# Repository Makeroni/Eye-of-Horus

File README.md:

# Eye-of-Horus

Eye of Horus is an open source platform to control any device just looking at them. The project (hardware & software) was built from scratch during the Space Apps Zaragoza to solve the Space Wearables challenge. This device could help engineers from NASA and astronauts on their tasks. The system combines eye tracking with a frontal camera to know where you are looking. The target devices are identified using light beacons (similar to LiFi technology) and controlled with wireless protocols.

![Logo][logo] Interacting with objects just looking at them has always been a dream for humans.

NASA engineers doing lab and field work often need to operate with computers and other tools but in some situations this interaction is not easy and may cause them to interrupt their activities. The absence of gravity hinders the mobility of the astronauts inside the station and may affect their work and safety. We accepted the Space Apps challenge for creating a wearable accessory that could help people interacting with computers, electronic devices and also everyday things just looking at them.

1. **Challenge:** The challenge is to design and build a wearable accessory that could be useful for the NASA ground engineers and also astronauts in their lab or field activities. The device would facilitate their work through a natural interface so they can do different things without using their hands. Thanks to it, they will be able, for instance, to interact with a distant control panel just looking at it.

2. **Wearables:** Wearable refers to the set of electronic devices which are incorporated in any part of our body that continuously interact with the user and other devices in order to perform a specific function. Smart watches, sports shoes built-in with GPS and bracelets that monitor our health are examples of this technology which is increasingly present in our lives. One of the best known wearables is Google Glass. Our device could be designed as an accessory to use with Google Glass to simplify the hardware and reduce its costs.

3. **3D printing:** The device must be durable and made from a non-brittle material. Due to this, we have decided to make it using 3D printers. This technology is cheap and easy to build so the device could be replicated worldwide or even in the space. NASA engineers could improve the device in their labs in a minute and astronauts could produce or fix it using the 3D printers at the station.

4. **Open Source:** We believe open knowledge is contributing to a better world and Eye of Horus is designed as an open source platform, both hardware and software.
The schematics and the implemented software can be found in the project Github repository, allowing people to modify, improve and redistribute their contributions.

5. **Internet of Things:** The Internet of Things (IoT) is a growing trend that extends internet connectivity beyond traditional devices like computers, smartphones and tablets to a diverse range of devices and everyday objects. This revolution increases the possibilities of the Eye of Horus allowing you to control the light level of your kitchen or turning on the coffee machine just using your vision. Therefore, the device must have built-in wireless capabilities, which is the base of IoT.

6. **Low Cost Solution:** We have developed a simple and low cost solution to detect and identify the objects in our surrounding. Infrared leds are used as light beacons (similar to LiFi technology) emitting different frequency pulses for each device (PC, camera, TV, microwave...). The frontal camera of our dispositive detects this light, differentiating and communicating the objects when you look at them.

# APPLICATIONS

Eye of Horus lets you interact with devices and objects just looking at them. The main application in the current challenge is to improve the work and safety of the NASA ground engineers and astronauts but this device could also make common people's lives easier:

- -Disability. People with functional diversity or who is hospitalized could use it to perform tasks which would be impossible due to their reduced mobility.

- -Driving safety and control. Thanks to our device, drivers could interact with the radio or car phone with both hands on the wheel. Their eyes could be also monitored to detect drowsiness or lack of attention on the road and prevent a potential accident.

- -Entertainment. It could be used as an eye-controlled mouse to play video games and position the targets just looking at them.

# HARDWARE

The hardware development efforts were split in two different branches:

- 1) Design and fabrication of the 3D printed case and frame.

- 2) Design and assembly of the required electronic components.

### Rubén Martín, member of Eye of Horus:

> The hardware is HARD!

 **3D Printing** 

The casing was designed to integrate the electronic components of the system. It consists of several 3D printed pieces to hold and position the camera, the infrared lights and allocate the electronics and batteries.  The complete 3D model can be viewed online in the following [link](http://p3d.in/e/JN2Oy+load).

We started with a simple design that has been improved to the current version:

- *Version 1*: The first goal was to design and fabricate a case which could be fitted as an accessory of the Google Glass. A replica was 3D printed as we did not have an actual product. The casing consists of a small box containing the battery and the processor connected through an USB wire to the camera. An articulated tube which ends in the camera holder and the infrared lights allows the system to be mobile and frame the eye pupil.

- *Version 2*: In the second version, which is the end of this prototype, the molding of the glasses is independent and functional without the need of the Google Glass. The look and the fastening system of the electronic components have been improved in this second version.

![Designed frame and casing][3d]

 **Electronic design** 

- **Eye Tracking device**

This part corresponds to the wireless system that captures and analyzes the eye pupil images under infrared illumination.

During the development process, several iterations have been made improving the prototype features and finally designing a printed circuit board (PCB) that could be manufactured with a low cost.

***Prototype 1***: A first prototype was built over the table with no case to test hardware and software.

![Prototype image][proto1]

The parts used in the different prototypes are common:

-  [VoCore v1.0](http://vocore.io/):  VoCore is a coin-sized Linux computer with wireless capabilities. It is also able to work as a fully functional router. It runs OpenWrt on top of Linux and contains 32MB SDRAM, 8MB SPI Flash and using 360MHz MIPS processor.

- Power circuit: It includes a system DC/DC which supply 5V to the circuit thanks to a lithium battery

- [Camera](http://www.alibaba.com/product-detail/7-1mm-mini-video-endoscope-camera_515483490.html): an small size USB endoscope camera was disassembled to remove the infrared blocking filter and replace it with a band pass filter with the oposite effect. This task was complicated due to the small size of the optical elements.

![Removing camera filter][camera]

- IR leds: infrared leds are responsible to illuminate the eye. The pupil is an aqueous medium that absorbs this light and results in a dark spot clearly visible in the images.

- Bandpass filter: a lens that filters the non-infrared frequencies of light emphasize the monochrome effect and prevents ambient light from affecting the system.

***Prototype 2***: Once the basic software and hardware was validated, a second version was developed to complete and integrate the system using the 3D printing models of the first version of the casing.

![Prototype image][proto2]

The system was modified to overcome the following hardware problems:

- Remove the electronic noise emitted by WiFi shield that affects data transmission in the camera wire.

- Correct the placement, orientation and intensity of the infrared LEDs for a correct eye pupil illumination.

All electronics components of the prototype were replicated in the second version to get a better finish of the product.

![Prototype image][proto3]

![Prototype image][proto4]

The assembly is the result of the first model of the product. It could be an addition to Google Glass using its front camera like a data gathering system of the physical world.

***Prototype 3***: On this part, a printed circuit board was designed based on the information obtained from the previous prototypes. It would allows a low cost and replicable electronic device. 

![Designed printed circuit boards][schematics]

This is a open source project, so all schematics are available. Anyone can download, edit and manufacture the device.

- **Light beacon device**

A prototype was designed using infrared flashlight pulses with adjustable frequency. This light, only visible in the front camera thanks to a band-pass filter, allow to differentiate the targeted devices.

![Light beacon device][beacon]

The system also integrates a bluetooth low energy (BLE) module which can receive requests from other devices. In our case, a computer linked with other BLE module is in charge of sending the turn on/off request when the main device indicates that the user is in front of the object and the eye tracking reveals that is looking at the beacon (in the example it would be a light lamp).

![Infrared images][ir]

The integrated components in this prototypes are:

- [Serial Bluetooth 4.0 BLE Module](http://www.tinyosshop.com/index.php?route=product/product&product_id=705): responsible for the communication of BLE with PC.

- [Relay control module](https://www.sparkfun.com/products/11042): to control a device connected to the network

- [Arduino Pro mini](http://www.arduino.cc/en/pmwiki.php?n=Guide/ArduinoProMini): the main microcontroller in charge of communicating with other modules and components.

- Infrared LED: responsible for carrying out the lighting flash.

# SOFTWARE

Our final goal is to obtain an autonomous device but during the weekend the software development was divided in two blocks: server and client. Server software is running inside the Eye of Horus while the client is running on a laptop computer.

**Server**

![Testing OpenWrt in the Vocore][openwrt]

This part of the software is executed in the VoCore module, a coin sized linux computer suitable for many  applications. This module acts as a server running OpenWrt, a Linux distribution for embedded devices.

The server software is in charge of:

- Capturing the video captured by the camera

- Streaming the data over WiFi using a lightweight webserver

**Client** 

![HTML5 eye interface][eyeint]

This part is in charge of:

- Receiving the video stream

- Processing the images of the eye in order to detect the center of the pupil

- Provide a user interface to calibrate the system

- Control the mouse in the laptop computer according to the coordinates dictated by the eye

The video stream in the client was processed in real time using HTML5. A segmentation library was developed from scratch to threshold the images and analyze its morphology to detect the pupil and compute its center of mass.

![Developed real time image segmentation library][code]

At this point, the user has a mouse controlled by his eye and can interact with any 3rd party software installed in the computer.

A demo of the client sofware recognizing the center of the pupil can be seen in our [website](http://makeronilabs.com/sites/nasa/eye_of_horus_interface/). You can play with the range selectors in order to see how it affects the recognition and reach optimal calibration when only the pupil is highlighted. The system will consider the center of gravity of the highlighted area as the coordinates where the eye is pointing. Calibration is very important and it may depend of the illumination. Thats the reason why the Eye of Horus has 4 leds illuminating the area of the eye. The pupil detection system has proven to be quite robust with the illumination provided by the device.

# DEMOS

Here you can find some examples of use:

 [Eye of Horus - Open Source Eye Assistance](https://vimeo.com/125373219) 

 [Eye of Horus Demo 1](https://vimeo.com/125396508) 

 [Eye of Horus Demo 2](https://vimeo.com/125396713) 

 [Eye of Horus Demo 3](https://vimeo.com/125396803) 

 [Eye of Horus Demo 4](https://vimeo.com/125396891) 

# FUTURE

The most important part of this project is the viability and profitability. We believe this project is highly sustainable. We can create a crowdfunding campaign using all the documentation.

### Borja Latorre, member of Eye of Horus:

>Never think about the future because it comes soon.

![The future][future]

We have the support of the City of Zaragoza and other incubators project to move forward. We also collaborate with numerous technological associations in our city. We have succeeded in 48 hours a functional prototype to show our system. It is easy to build, cheap and technological.

### Jose Luis Berrocal, member of Eye of Horus

> People say that space is unlimited. We also believe that our project has no limits. 

# OUR SPACE APPS WEEKEND:

During this amazing weekend we met very nice people, participated in one of the most important experiences of our lives, learning at every moment and developing after 48 hours of hard work a final product. 

![Our space apps weekend][weekend]

### Luis Martín, member of Eye of Horus

> A unique experience, an amazing team and an impressive project. 

Here you can see our weekend and several milestones that have marked the achievement of the project:

- **SATURDAY**: 

- **9:00**: Space Apps Zaragoza START.

- **10:00**: Make your team, present your idea: We want to participate in the Wearables Challenge developing a real product involving hardware and software.

- **10:30**: Brainstorming: We have a 3D printer, some microcontrollers, electronics components, a solder... what can we do?.

- **11:00**: State of the art: We decide to create a device to eye tracking monitoring capable to control any electrical device mixing the tracking of the eye and a frontal camera that analyze the real world. We start searching some information about actual application of this technology and other similar projects.

- **11:30**: Meeting: We show the information collected to the team.

- **11:45**: Hardware: We design a first assemble (VOCORE board, DCDC board, battery and camera) to bring to the software developers a prototype to work with it.

- **12:00**: Software: We start to program the main code. This HTML code control and track the eye movements.

- **12:00**: Hardware: We create a 3D design of the first prototype. We develop the electronic case and the structure for placing the camera system on the head of a person.

- **12:45**: 3D printing: Our 3D printer (TAZ4 Lulzbot) start to print the first samples of the case. We rebuild the designs in other to improve our models.

- **13:45**: Software: We finish the basic code in HTML5 to track the eye movement.

- **14:00**: It is time to eat….PIZZA!! and talk with other team about their projects. Co-working 100% Thanks to the Space Apps Zgz organization.

- **14:30**: Meeting: We define the next millestones of the project. We decide to create a web interface to calibrate the device.
- **15:00**: 3D printing: We improve our designs in order to build the first version of the case. We print it!

- **15:30**: Software: We want to control the mouse of the computer with our eye as a example of application. We design a web interface to test and calibrate the device. 

- **17:00**: Hardware: We finish the power circuit assembly for the first prototype.

- **18:00**:  Software: We develop the web interface and the PHP code. This code is used to control the PC mouse using our eye track.

- **19:00**:  Documentation: We start to documentate all the software.

- **20:00**: It is time to eat….PIZZA AGAIN!! Night is coming in Zaragoza.

- **22:00**:  Night meeting: We talked about what happened during the day.

- **00:00**: We go to Makeroni space (a local technological association) to finish the first hardware prototype in the night.

- **SUNDAY**: 

- **4:00**: It is time to sleep

- **9:00**: Begins the second and final day. A cup of coffee and the batteries recharged.

- **10:30**: Meeting: We start the day with a real prototype and the basic software. This day we want to control a light, our computer and the TV with the eye like an example of use to use it for the presentation.

- **11:00**: Hardware: We have a lot of noise in the camera signal in the prototype. We can not continue working. We start to investigate where is the problem.

- **11:30**: Software: We use Processing IDE to create some examples of applications. 

- **11:45**: Hardware: The device still fails. We dismount the system piece by piece to find the error.

- **12:00**: Presentation: The presentation is a very important point in this event. We start before lunch.

- **12:00**: Software: We want to show our eye in the presentation and control it with our eye. So we decide to make the presentation with Reveal JS / HTML.

- **13:45**: Hardware: After several test and changes (battery, microcontroller, dcdc circuit) we find the problem. The wifi in our device makes a loud noise and the cable used was not shielded.

- **14:00**: The last meal before the presentations .... it could not be any other thing than PIZZA!!

- **14:30**: Presentation: We still working in a "amazing" presentation with slide eye control but we need a functional prototype.

- **15:00**: Software: We modify Reveal JS presentation to add the eye tracking function.

- **15:30**: Software: We want to control the mouse of the computer with our eye as a example of application. We design a web interface to test and calibrate the device. 

- **17:00**: General: We prepare hardware and software for the final part of the event.

- **18:00**:  PRESENTATION TIME: It's time to present our project to all attendees and prove that Eye of Horus is the best.

- **20:00**: Finish one of the best experiences of our lives.

# ABOUT US

The four members of the team have different technological backgrounds as electronic engineering, physics and computer science but we all share passion for making all kind of inventions mixing any available technology.

We are all members of [MAKERONI LABS](http://makeronilabs.com), a non profit that was born in Zaragoza in 2012 following the MAKER movement that is currently shaking the world.

Its main purposes are:

- Promote a collaborative workspace for the development of new technologies.

- Promote the dissemination of new technologies; both projects developed by members of the association, as other people. 

To fulfill these purposes are working on:

- Create and maintain a physical or virtual, collaborative work space.

- Promote and coordinate the development of technological projects for companies and individuals, by members of the association.

- Promote the capacities of members of the association in competitions, talks and exhibitions.

- Conduct outreach to the diffusion of new technologies activities.

### Makeroni Team

> We did this Open Source project for the Space Apps Challenge 2015. 
> We hope you will like it, use it for your inventions and in any way contribute to the project!

# MORE INFO

The Eye Of Horus project in our site: [Eye of Horus Project](http://makeronilabs.com/proyectos/37-eye-of-horus-open-source-eye-assistance) 

[logo]: http://makeroni.github.io/Eye-of-Horus/img/logo.png
[3d-model]: http://makeroni.github.io/Eye-of-Horus/img/3d-model.gif
[proto1]: http://siminelaki.org/noname/nasa/photos/prototype-0.png
[proto2]: http://siminelaki.org/noname/nasa/photos/prototype-1.png
[proto3]: http://siminelaki.org/noname/nasa/photos/prototype-2.png
[proto4]: http://siminelaki.org/noname/nasa/photos/prototype-3.png
[beacon]: http://siminelaki.org/noname/nasa/photos/prototype-4.png
[eyeint]: http://siminelaki.org/noname/nasa/photos/prototype-5.png
[future]: http://siminelaki.org/noname/nasa/photos/future.png
[weekend]: http://siminelaki.org/noname/nasa/photos/weekend.png
[schematics]: http://siminelaki.org/noname/nasa/photos/schematics.png
[3d]: http://siminelaki.org/noname/nasa/photos/3d-model.png
[openwrt]: http://siminelaki.org/noname/nasa/photos/openwrt.png
[ir]: http://siminelaki.org/noname/nasa/photos/ir.png
[camera]: http://siminelaki.org/noname/nasa/photos/camera.png
[code]: http://siminelaki.org/noname/nasa/photos/code.png

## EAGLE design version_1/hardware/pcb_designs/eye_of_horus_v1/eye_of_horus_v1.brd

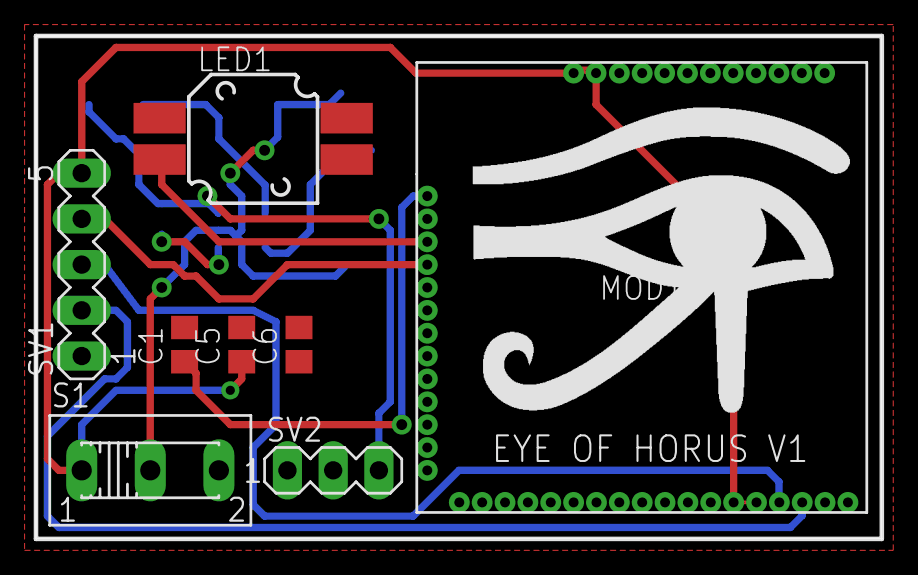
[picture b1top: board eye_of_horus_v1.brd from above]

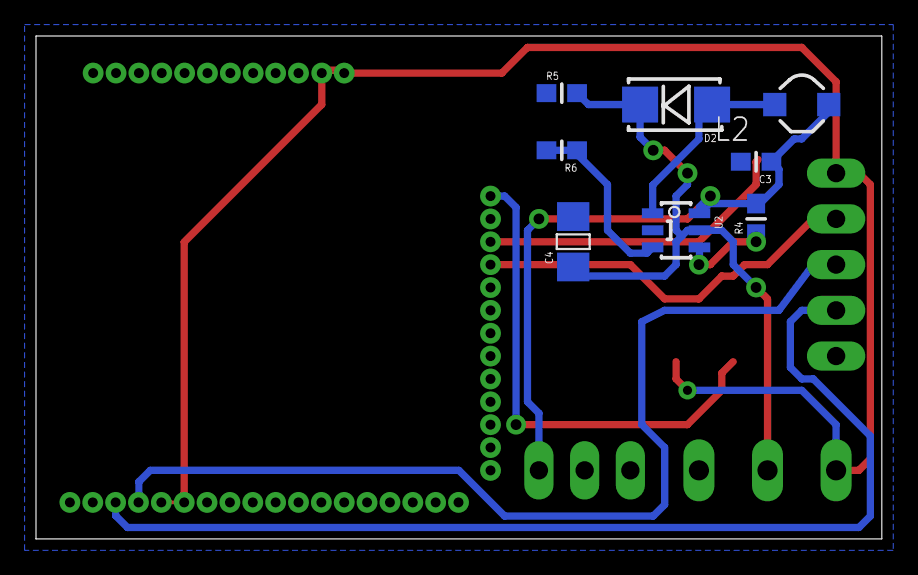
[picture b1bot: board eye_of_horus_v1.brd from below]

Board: 2 copper layers, 47.0 x 27.9 mm, 16 parts (8 on the bottom side), 12 nets.

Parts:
C1, C5, C6: C0805
C3: 10uF; 0603
C4: 22uF; 1206
D2: MBRA210LT3G; SMA-DIODE
L2: 2.2uH; 1_3X1_3
LED1: LEDLUMILED; LUMILED
MOD1: VOCORE_V10A
R4: 1M; 0603
R5: 95.3K; 0603
R6: 30.9K; 0603
S1: 255SB
SV1: MA05-1
SV2: MA03-1
U2: LTC3426; SOT23-6

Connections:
1V8: C1.1, MOD1.W1
5V: C5.1, MOD1.N1, MOD1.N2, MOD1.S13, MOD1.S14, S1.1, SV1.5
GND: C1.2, C3.2, C4.2, C5.2, C6.2, LED1.4-, MOD1.N3, MOD1.N4, MOD1.S17, MOD1.S18, R6.1, SV1.1, SV2.2, U2.2
GP09: LED1.2+, MOD1.W3
GP22: MOD1.W4, SV1.4
unnamed: D2.A, L2.P$2, U2.1
unnamed: R4.1, U2.4
unnamed: C4.1, D2.C, R5.2, S1.2, U2.5
unnamed: R5.1, R6.2, U2.3
USB_N: MOD1.S15, SV1.3
USB_P: MOD1.S16, SV1.2
VBAT: C3.1, L2.P$1, R4.2, SV2.3, U2.6

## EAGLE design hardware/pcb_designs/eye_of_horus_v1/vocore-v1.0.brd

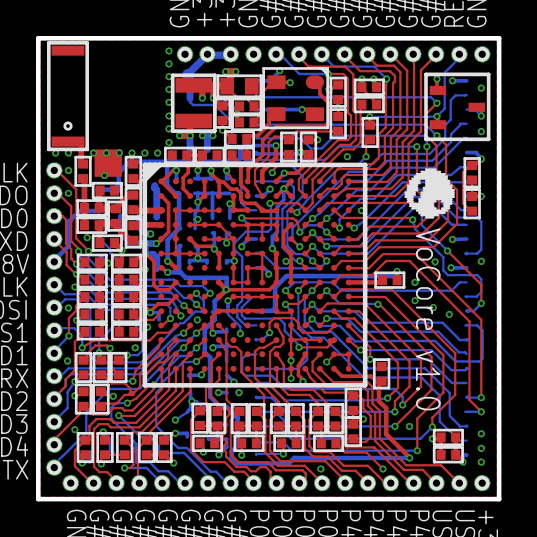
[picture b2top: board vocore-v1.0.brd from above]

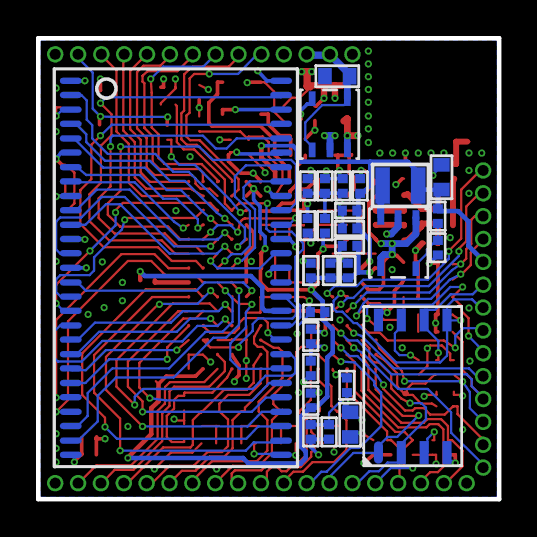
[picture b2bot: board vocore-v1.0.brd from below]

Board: 4 copper layers, 25.6 x 25.6 mm, 146 parts (29 on the bottom side), 113 nets.

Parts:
C2, C4, C6, C7, C8, C9, C10, C14, C15, C16, C17, C18, C35, C36, C37, C38, C40, C42, C43, C48, C50, C77, C79, C84, C92, C93, C98, C104, C108, C109, C110, C111, C112, C113, C114, C161, C251, C279, C387, C388, C389, C390, C391, C414, C422, C443: 0402; 0402_1PRIMARY
C103, C105, C106, C107: 0603; 0603_1PRIMARY
CON2: 5020; 5020_1PRIMARY
D1: 0402; 0402_1PRIMARY
L11, L12: 0402; 0402_1PRIMARY
L14, L15: 0806; 0806_1PRIMARY
PB00, PB01, PB02, PB03, PB04, PB05, PB06, PB07, PB08, PB09, PB10, PB11, PB12, PB13, PB14, PB15, PB16, PB17, PB18: PORT_1PIN_DECAL; PORT_1PIN_DECAL_1PRIMARY
PL01, PL02, PL03, PL04, PL05, PL06, PL07, PL08, PL09, PL10, PL11, PL12, PL13, PL14: PORT_1PIN_DECAL; PORT_1PIN_DECAL_1PRIMARY
PT01, PT02, PT03, PT04, PT05, PT06, PT07, PT08, PT09, PT10, PT11, PT12, PT13, PT14: PORT_1PIN_DECAL; PORT_1PIN_DECAL_1PRIMARY
R1, R8, R26, R27, R28, R29, R50, R55, R56, R57, R58, R67, R68, R69, R70, R71, R94, R95, R107, R118, R119, R142, R144, R150, R154, R189, R192, R193, R212, R293, R300, R308, R318: 0402; 0402_1PRIMARY
SR1, SR2: 0402; 0402_1PRIMARY
TEST1: TEST_POINT_GND; TEST_POINT_GND_1PRIMARY
U1: TFBGA196; TFBGA196_1PRIMARY
U3: SO8; SO8_1PRIMARY
U8, U9: LDO1; LDO1_1PRIMARY
U25: U4; U4_1PRIMARY
U33: Y1; Y1_1PRIMARY
U35: TSOP2-54P-400MIL; TSOP2-54P-400MIL_1PRIMARY

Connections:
1V8_FB: R67.1, R68.2, U8.5
1V8_SW: L14.1, U8.3
3V3_FB: R69.2, R70.1, U9.5
3V3_SW: L15.1, U9.3
$$$22498: U1.7, U33.1
$$$22629: C15.2, R212.1, U33.3
+1.2V: C16.1, C93.1, C98.1, C104.1, C109.1, C110.1, C111.1, U1.10, U1.23, U1.24, U1.79, U1.85, U1.93, U1.103, U1.107, U1.117, U1.195
+1.8V: C2.1, C106.1, C108.1, C161.1, L14.2, PL05.1, R68.1, U1.8, U1.86
+3.3V: C9.1, C17.1, C42.1, C84.1, C92.1, C105.2, C107.1, C112.1, C113.1, C114.1, C251.2, C387.1, C388.1, C389.1, C390.1, C391.1, C414.1, C422.1, C443.2, L15.2, PB18.1, R69.1, R71.1, R144.1, R192.2, R293.1, SR2.1, U1.9, U1.15, U1.52, U1.57, U1.59, U1.75, U1.80, U1.89, U1.94, U1.100, U1.108, U1.114, U1.131, U1.132, U1.133, U1.134, U1.179, U3.8, U8.1, U8.4, U25.3, U35.1, U35.3, U35.9, U35.14, U35.27, U35.43, U35.49
+5V: C103.1, PT02.1, PT03.1, U9.1, U9.4
EPHY0R_RC: C48.1, R26.2, R28.2
EPHY0T_RC: C50.1, R27.2, R29.2
EPHY4R_RC: C79.1, R56.2, R58.2
EPHY4T_RC: C77.1, R55.2, R57.2
EPHY_RES: R50.2, U1.186
GND: C2.2, C4.2, C6.2, C7.2, C8.2, C9.2, C10.1, C14.1, C15.1, C16.2, C17.2, C18.1, C40.2, C42.2, C43.2, C48.2, C50.2, C77.2, C79.2, C84.2, C92.2, C93.2, C98.2, C103.2, C104.2, C105.1, C106.2, C107.2, C108.2, C109.2, C110.2, C111.2, C112.2, C113.2, C114.2, C161.2, C251.1, C387.2, C388.2, C389.2, C390.2, C391.2, C414.2, C422.2, C443.1, D1.2, L11.2, PB00.1, PT01.1, PT04.1, PT14.1, R1.2, R8.1, R50.1, R67.2, R70.2, R94.2, R95.2, R107.2, R118.1, R119.2, R142.1, R150.1, R154.2, R308.2, R318.2, TEST1.1, U1.1, U1.4, U1.16, U1.18, U1.30, U1.31, U1.32, U1.33, U1.44, U1.45, U1.46, U1.47, U1.48, U1.49, U1.50, U1.51, U1.58, U1.60, U1.61, U1.62, U1.63, U1.64, U1.65, U1.71, U1.72, U1.73, U1.74, U1.76, U1.77, U1.78, U1.90, U1.91, U1.92, U1.104, U1.105, U1.106, U1.118, U1.119, U1.120, U1.121, U1.135, U1.136, U1.150, U1.164, U1.165, U1.166, U1.178, U1.181, U1.182, U1.192, U1.196, U3.4, U8.2, U9.2, U25.2, U33.2, U33.4, U35.6, U35.12, U35.28, U35.41, U35.46, U35.52, U35.54
GPIO0: PT09.1, U1.26
I2C_CLK: PT12.1, U1.28
I2C_SD: PT11.1, U1.27
JTAG_CLK: PT07.1, U1.12
JTAG_RST: PT06.1, U1.11
JTAG_TDI: PT10.1, U1.14
JTAG_TDO: PT05.1, U1.25
JTAG_TMS: PT08.1, U1.13
LED0: PL03.1, R308.1, U1.129
LED1: PL09.1, R154.1, U1.141
LED2: PL11.1, R150.2, U1.144
LED3: PL12.1, R144.2, U1.155
LED4: PL13.1, R118.2, U1.158
LED_WLAN: R142.2, R193.2, U1.127
LED_WLAN+: D1.1, R193.1
P0RN: PB11.1, R26.1, U1.145
P0RP: PB10.1, R28.1, U1.159
P0TN: PB08.1, R27.1, U1.173
P0TP: PB09.1, R29.1, U1.187
P4RN: PB15.1, R56.1, U1.177
P4RP: PB14.1, R58.1, U1.191
P4TN: PB12.1, R55.1, U1.163
P4TP: PB13.1, R57.1, U1.149
RESET: PT13.1, R189.2, U25.1
RESET_PORST: R189.1, U1.38
SDRAM_A0: U1.98, U35.23
SDRAM_A1: U1.111, U35.24
SDRAM_A2: U1.110, U35.25
SDRAM_A3: U1.109, U35.26
SDRAM_A4: U1.126, U35.29
SDRAM_A5: U1.125, U35.30
SDRAM_A6: U1.124, U35.31
SDRAM_A7: U1.140, U35.32
SDRAM_A8: U1.139, U35.33
SDRAM_A9: U1.123, U35.34
SDRAM_A10: U1.154, U35.22
SDRAM_A11: U1.138, U35.35
SDRAM_A12: U1.153, U35.36
SDRAM_BA0: U1.152, U35.20
SDRAM_BA1: U1.168, U35.21
SDRAM_CAS: U1.40, U35.17
SDRAM_CKE: R293.2, U1.39, U35.37
SDRAM_CLK: R300.2, U35.38
SDRAM_CS: U1.137, U35.19
SDRAM_D0: U1.66, U35.2
SDRAM_D1: U1.53, U35.4
SDRAM_D2: U1.54, U35.5
SDRAM_D3: U1.55, U35.7
SDRAM_D4: U1.56, U35.8
SDRAM_D5: U1.67, U35.10
SDRAM_D6: U1.81, U35.11
SDRAM_D7: U1.68, U35.13
SDRAM_D8: U1.82, U35.42
SDRAM_D9: U1.69, U35.44
SDRAM_D10: U1.70, U35.45
SDRAM_D11: U1.95, U35.47
SDRAM_D12: U1.96, U35.48
SDRAM_D13: U1.83, U35.50
SDRAM_D14: U1.97, U35.51
SDRAM_D15: U1.84, U35.53
SDRAM_DQML: U1.122, U35.15
SDRAM_DQMU: U1.167, U35.39
SDRAM_R51: R300.1, U1.112
SDRAM_RAS: U1.151, U35.18
SDRAM_WE: U1.41, U35.16
SPI_CLK: PL06.1, SR1.2, U3.6
SPI_CLK_L: R94.1, SR1.1, U1.169
SPI_CS0: PB06.1, U1.183, U3.1
SPI_CS1: PL08.1, U1.142
SPI_HOLD: R71.2, U3.7
SPI_MISO: PB05.1, U1.156, U3.2
SPI_MOSI: PL07.1, R95.1, U1.115, U3.5
SPI_WE: SR2.2, U3.3
UARTF_CTS: PL02.1, U1.130
UARTF_DCD: PL01.1, U1.116
UARTF_DSR: PL10.1, U1.143
UARTF_DTR: PB07.1, U1.172
UARTF_RIN: PL14.1, U1.157
UARTF_RTS: PB02.1, U1.184
UARTF_RXD: PB03.1, R192.1, U1.171
UARTF_TXD: PL04.1, R119.1, U1.128
UARTL_RXD2: PB04.1, R318.1, U1.185
UARTL_TXD2: PB01.1, R107.1, U1.170
UPHY_RES: C43.1, R8.2, U1.193
USB_M: PB16.1, U1.180
USB_P: PB17.1, U1.194
WL_ANT: C36.2, C279.1, L12.2
WL_ANT_C: C279.2, CON2.2
WL_RF0_OUTL: C35.2, C36.1, C37.1, L11.1
WL_RF0_OUTN: C38.1, U1.43
WL_RF0_OUTP: C35.1, U1.29
WL_RF0_OUTR: C37.2, C38.2, C40.1, L12.1
WL_V12_CAP: C4.1, C6.1, C7.1, C8.1, U1.5, U1.17, U1.19, U1.36, U1.37
WL_V12_PLL: C14.2, U1.20, U1.34, U1.35
WL_V12_RES: C10.2, R1.1, U1.22
WL_V33: C18.2, U1.6
WL_X2: R212.2, U1.21

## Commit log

2015-04-16 Improve the eye interface
2015-04-16 Hardware folder
2015-04-18 Rename 3d model folder
2015-04-18 Create gh-pages branch via GitHub
2015-04-18 Add logo image
2015-04-18 fix for the README file
2015-04-18 resize logo image
2015-04-18 add 3d model animated gif
2015-04-18 add black spot
2015-04-19 Rename folders
2015-04-19 Renamed software folder
2015-04-19 Arduino Light Relay
2015-04-19 Processing example. Discovery spaceship across the solar system.
2015-04-20 Processing example. Arduino light relay example.
2015-09-20 Reorder folders
2015-09-20 Version 2
    Major changes in Hardware and Software
2015-09-20 EoH - Switch on & switch off the light
    Demo showing how to switch on and switch off a light with the eye using
    The Eye of Horus
2015-09-29 Playing sounds with the eye
2015-09-30 Adjusted frequency range
2015-10-02 Demo 3 - EoH theremin.
    X Frequency. Y Amplitude
